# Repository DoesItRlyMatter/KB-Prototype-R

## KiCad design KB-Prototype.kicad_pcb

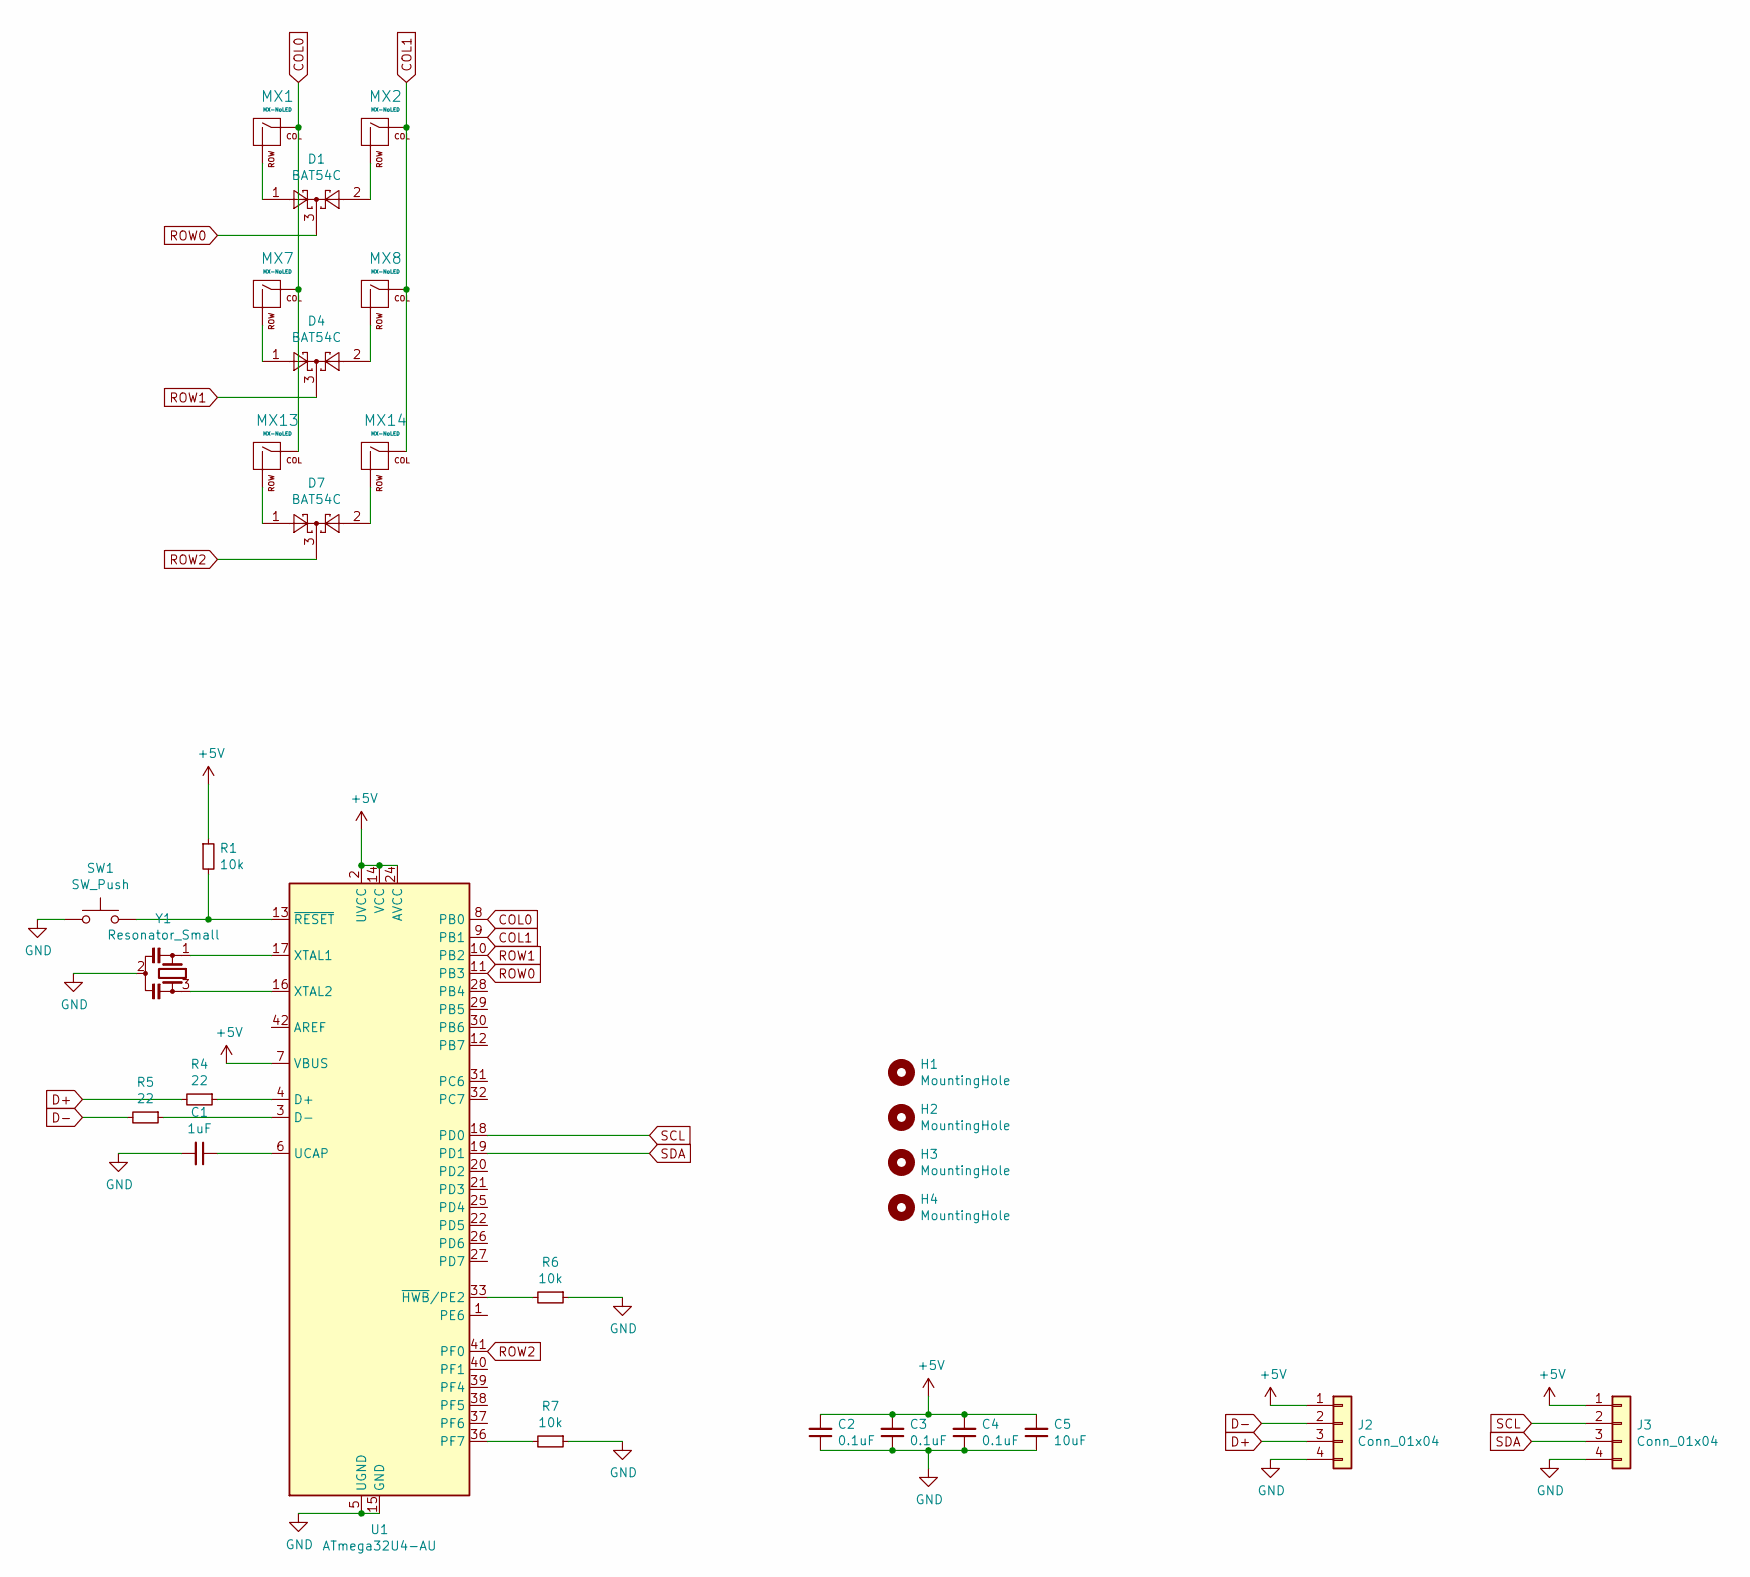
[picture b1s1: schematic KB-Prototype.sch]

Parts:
C1: 1uF; C_0805_2012Metric
C2, C3, C4: 0.1uF; C_0805_2012Metric
C5: 10uF; C_0805_2012Metric
D1, D4, D7: BAT54C; SOT-23
H1, H2, H3, H4: MountingHole; Generic-Mounthole
J2, J3: Conn_01x04; JST-SR-4
MX1, MX2, MX7, MX8, MX13, MX14: MX-NoLED; MXOnly-1U-NoLED
R1, R6, R7: 10k; R_0805_2012Metric
R4, R5: 22; R_0805_2012Metric
SW1: SW_Push; SKQG-1155865
U1: ATmega32U4-AU; TQFP-44_10x10mm_P0.8mm
Y1: Resonator_Small; CSTCE

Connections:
+5V: C2.2, C3.2, C4.2, C5.2, J2.1, J3.1, R1.1, U1.2 (UVCC), U1.7 (VBUS), U1.14 (VCC), U1.24 (AVCC), U1.34 (VCC), U1.44 (AVCC)
COL0: MX1.1 (COL), MX7.1 (COL), MX13.1 (COL), U1.8 (PB0)
COL1: MX2.1 (COL), MX8.1 (COL), MX14.1 (COL), U1.9 (PB1)
D+: J2.3, R4.2
D-: J2.2, R5.2
GND: C1.2, C2.1, C3.1, C4.1, C5.1, J2.4, J3.4, R6.1, R7.1, SW1.1, U1.5 (UGND), U1.15 (GND), U1.23 (GND), U1.35 (GND), U1.43 (GND), Y1.2
unnamed: C1.1, U1.6 (UCAP)
unnamed: D1.1, MX1.2 (ROW)
unnamed: D1.2, MX2.2 (ROW)
unnamed: D4.1, MX7.2 (ROW)
unnamed: D4.2, MX8.2 (ROW)
unnamed: D7.1, MX13.2 (ROW)
unnamed: D7.2, MX14.2 (ROW)
unnamed: R1.2, SW1.2, U1.13 (~RESET)
unnamed: R4.1, U1.4 (D+)
unnamed: R5.1, U1.3 (D-)
unnamed: R6.2, U1.33 (~HWB~/PE2)
unnamed: R7.2, U1.36 (PF7)
unnamed: U1.16 (XTAL2), Y1.3
unnamed: U1.17 (XTAL1), Y1.1
ROW0: D1.3, U1.11 (PB3)
ROW1: D4.3, U1.10 (PB2)
ROW2: D7.3, U1.41 (PF0)
SCL: J3.2, U1.18 (PD0)
SDA: J3.3, U1.19 (PD1)

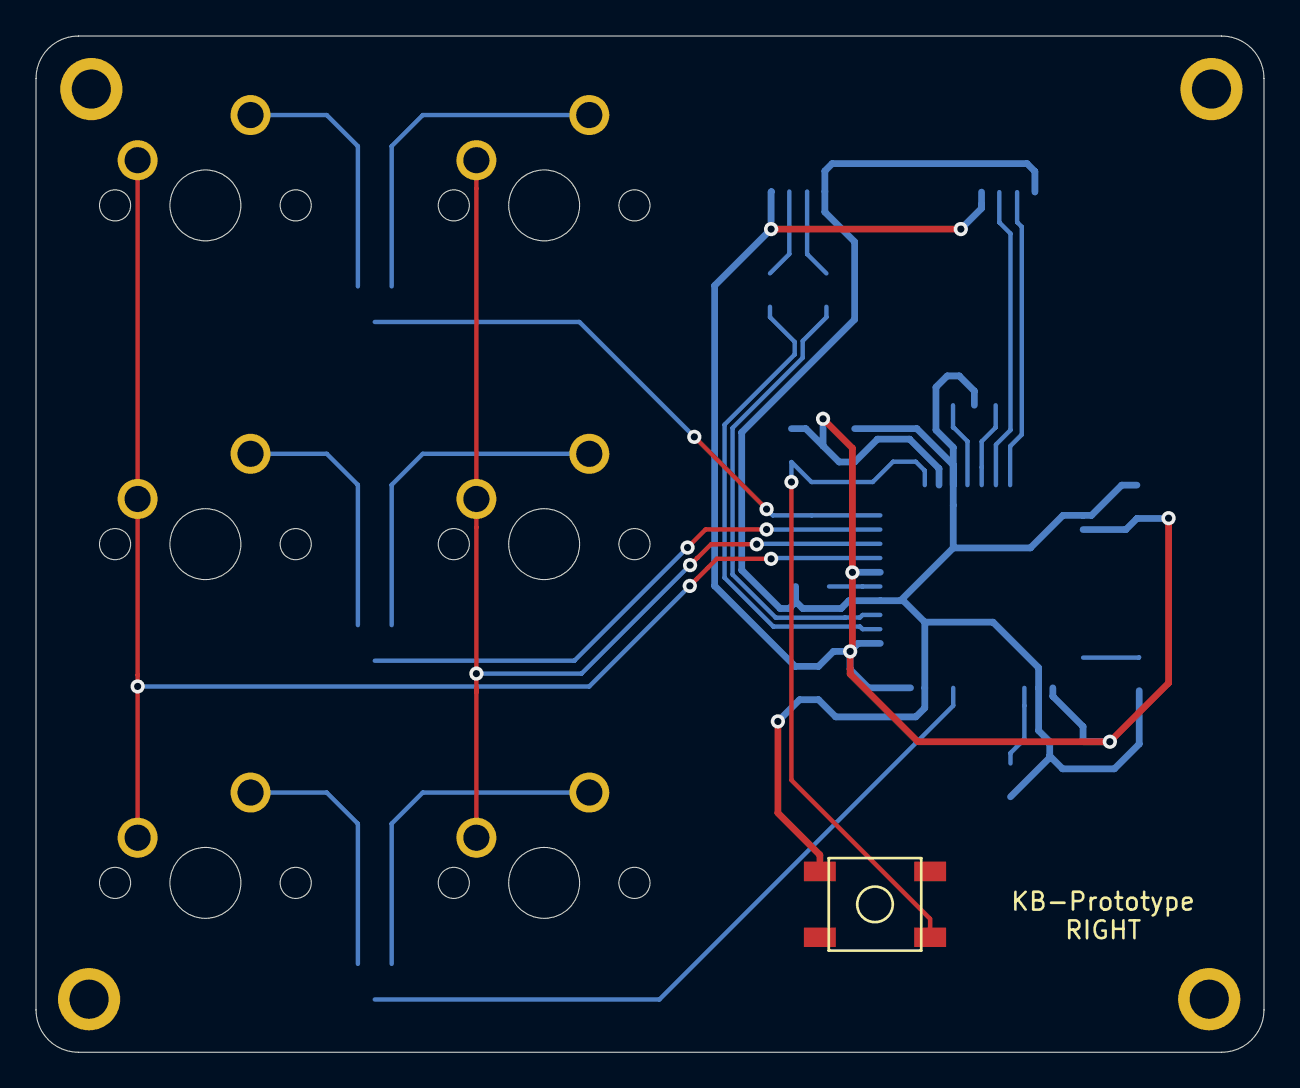
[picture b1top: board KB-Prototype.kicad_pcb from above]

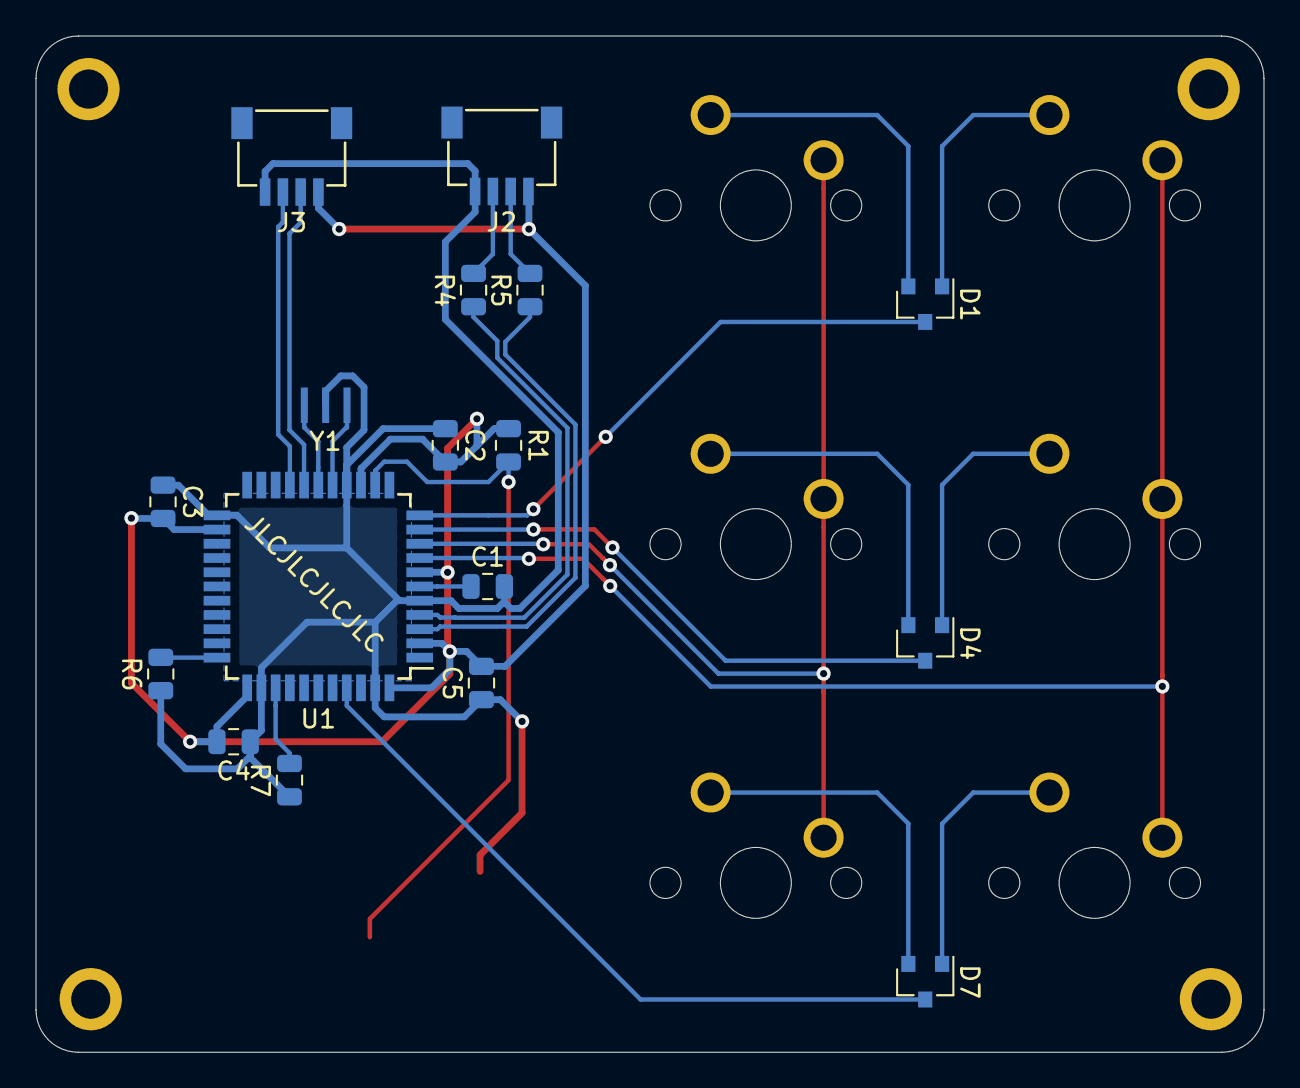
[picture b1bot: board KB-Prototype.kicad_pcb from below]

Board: 2 copper layers, 69.1 x 57.2 mm, 28 parts (17 on the bottom side), 25 nets.

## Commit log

2020-07-11 copied over left side
2020-07-11 modified sch to suit right half
2020-07-11 traced right half, added mounting holes
2020-07-12 generated gerbers
2020-07-12 zipped gerbers
